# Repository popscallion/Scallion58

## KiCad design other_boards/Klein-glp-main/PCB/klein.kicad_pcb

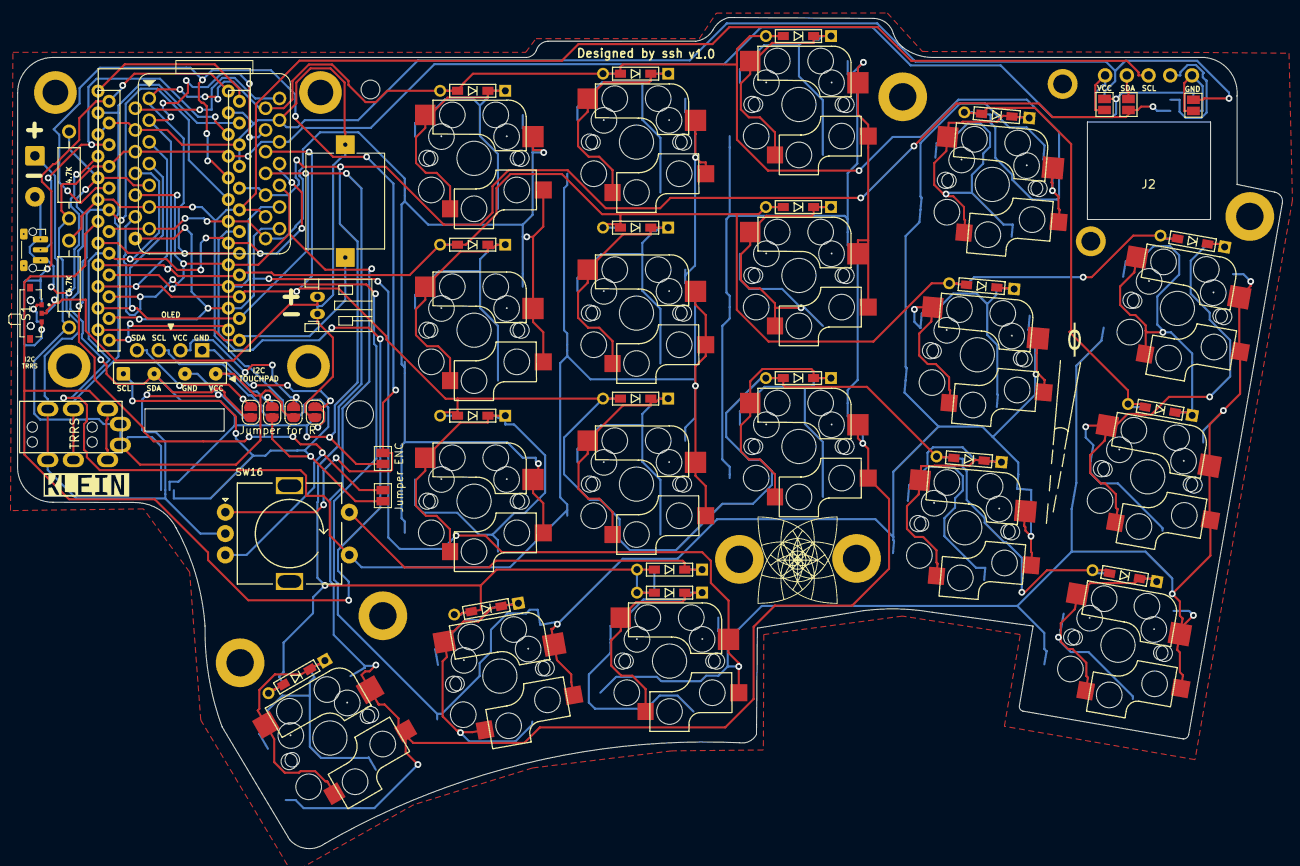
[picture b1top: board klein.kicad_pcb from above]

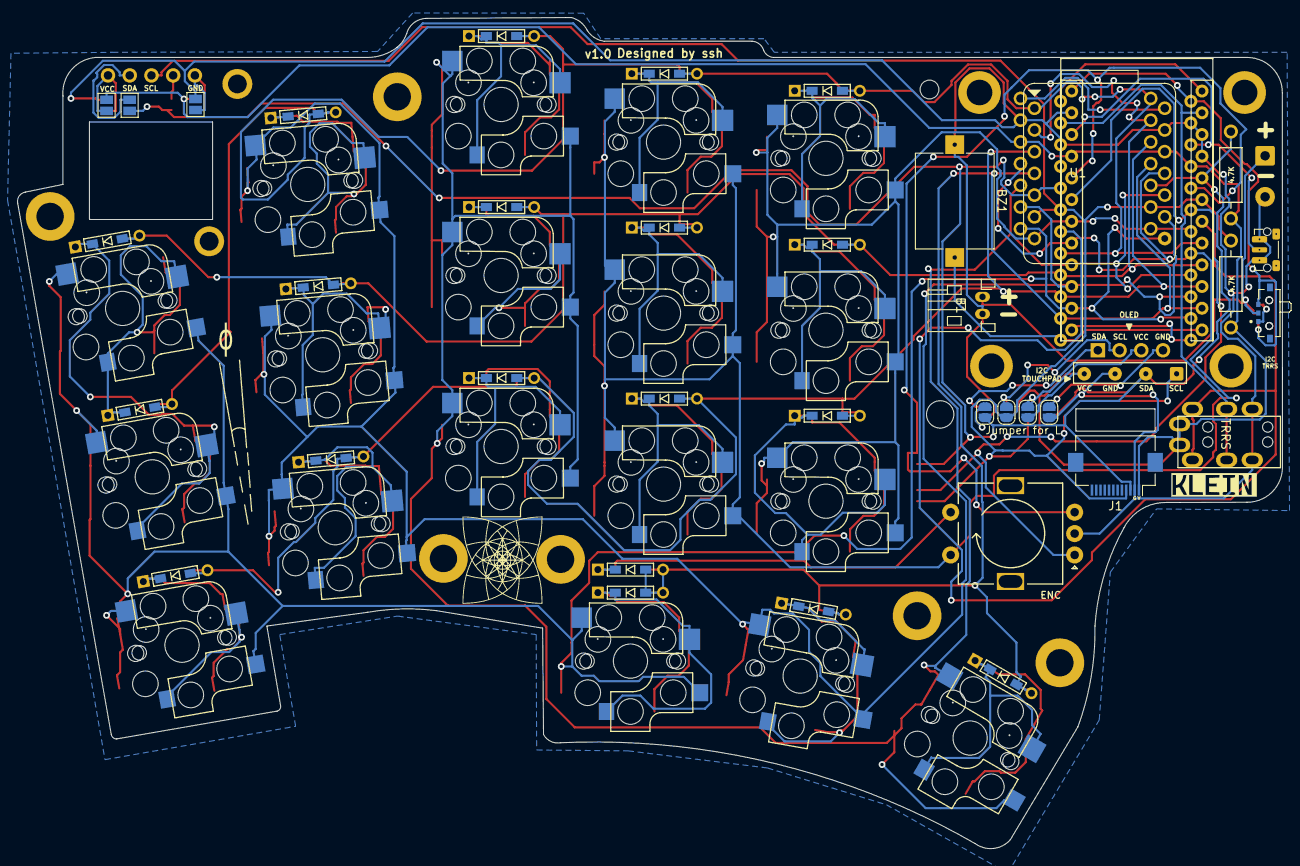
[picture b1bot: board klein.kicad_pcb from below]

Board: 2 copper layers, 147.9 x 97.2 mm, 83 parts (49 on the bottom side), 48 nets.

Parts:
B1: JST Battery; JST_PH_reversible
B2: Battery Pads; SolderWire-0.5sqmm_1x02_P4.8mm_D0.9mm_OD2.3mm
BZ1: Buzzer; Buzzer_Mallory_AST1109MLTRQ_reversible
D1, D2, D3, D4, D5, D6, D7, D8, D9, D10, D11, D12, D13, D14, D15, D16, D17, D18, D19: DIODE; D3_TH_SMD
G3, G4: LOGO; klein
G33, G34: LOGO; klein_small
H1, H2, H4, H5, H6, H8: MountingHole; MountingHole_3.2mm_M3_ISO7380_Pad
H3: MountingHole; MountingHole_3.2mm_M3
H7: MountingHole; MountingHole_2.2mm_M2
H9, H10: MountingHole; MountingHole_2.2mm_M2_ISO7380_Pad
J1: Conn_01x12; Hirose_FH12-12S-0.5SH_1x12-1MP_P0.50mm_Horizontal
J2: Haptic Buzz; Pimoroni Haptic Buzz DRV2605L Driver
J3: Conn_01x04; SolderWire-0.1sqmm_1x04_P3.6mm_D0.4mm_OD1mm
J5: OLED-128x64
JP1, JP2, JP3, JP4, JP5, JP6, JP7, JP8: Jumper_2_Open; SolderJumper-2_P1.3mm_Open_RoundedPad1.0x1.5mm
JP9, JP10: Jumper_2_Open; SolderJumper-2_P1.3mm_Open_Pad1.0x1.5mm
JP11, JP13: GND Jumper; SolderJumper-2_P1.3mm_Open_Pad1.0x1.5mm
JP12, JP14: VCC Jumper; SolderJumper-2_P1.3mm_Open_Pad1.0x1.5mm
JP16, JP17: SolderJumper_2_Open; SolderJumper-2_P1.3mm_Open_Pad1.0x1.5mm
R1, R2: 4.7K; RESISTOR
RSW1: SW_Push; SW_Push_1P1T-MP_NO_Horizontal_Alps_SKRTLAE010_both_sides
S1: EG1218; RevSlideSwitch
SW1, SW2, SW3, SW4, SW5, SW6, SW7, SW8, SW9, SW10, SW11, SW12, SW13, SW14, SW15, SW17, SW18, SW19: MX_SW_HS; MX_Choc_Hotswap_Mod
SW16: RotaryEncoder_Switch; MX-1U-EC11_Switch
T1: Trackpad_Mount; Trackpad Mount
U1: XIAO-BLE
U2: ProMicro; ProMicro_rev2
U3: TRRS; MJ-4PP-9

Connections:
AUDIO: BZ1.1 (-), U2.12 (9/B5)
BAT+: S1.3, U2.24 (RAW)
COL 0: SW1.1, SW6.1, SW11.1, U1.7 (PB08_A6_D6_TX), U2.18 (F6/A1)
COL 1: SW2.1, SW7.1, SW12.1, SW16.S1, U1.11 (PA6_A10_D10_MOSI), U2.17 (F7/A0)
COL 2: SW3.1, SW8.1, SW13.1, SW17.1, U1.10 (PA5_A9_D9_MISO), U2.16 (B1/15)
COL 3: SW4.1, SW9.1, SW14.1, SW18.1, U1.9 (PA7_A8_D8_SCK), U2.15 (B3/14)
COL 4: SW5.1, SW10.1, SW15.1, SW19.1, U1.8 (PB09_A7_D7_RX), U2.14 (B2/16)
ENC_A: JP9.2 (B), SW16.A, U2.20 (F4/A3)
ENC_B: JP10.2 (B), SW16.B, U2.19 (F5/A2)
GND: B1.2, B2.2 (-), BZ1.2 (+), J1.2, J3.3, JP1.2 (B), JP8.2 (B), JP11.1 (A), JP13.1 (A), RSW1.1, SW16.C, U1.13 (GND), U2.3 (GND), U2.4 (GND), U2.23 (GND), U3.S
unnamed: B1.1, B2.1 (+), S1.2
unnamed: D1.1 (K), SW1.2
unnamed: D2.1 (K), SW2.2
unnamed: D3.1 (K), SW3.2
unnamed: D4.1 (K), SW4.2
unnamed: D5.1 (K), SW5.2
unnamed: D6.1 (K), SW6.2
unnamed: D7.1 (K), SW7.2
unnamed: D8.1 (K), SW8.2
unnamed: D9.1 (K), SW9.2
unnamed: D10.1 (K), SW10.2
unnamed: D11.1 (K), SW11.2
unnamed: D12.1 (K), SW12.2
unnamed: D13.1 (K), SW13.2
unnamed: D14.1 (K), SW14.2
unnamed: D15.1 (K), SW15.2
unnamed: D17.1 (K), SW17.2
unnamed: D18.1 (K), SW18.2
unnamed: D19.1 (K), SW19.2
unnamed: J2.1, JP13.2 (B), JP14.2 (B)
unnamed: J2.2, JP17.1 (A)
unnamed: J2.4, JP16.1 (A)
unnamed: J2.5, JP11.2 (B), JP12.2 (B)
unnamed: J5.1 (GND), JP1.1 (A), JP5.1 (A)
unnamed: J5.2 (VCC), JP2.1 (A), JP6.1 (A)
unnamed: J5.3 (SCL), JP3.1 (A), JP7.1 (A)
unnamed: J5.4 (SDA), JP4.1 (A), JP8.1 (A)
RESET: RSW1.2, U2.22 (RST)
ROW 0: D1.2 (A), D2.2 (A), D3.2 (A), D4.2 (A), D5.2 (A), U1.1 (PA02_A0_D0), U2.8 (5/C6)
ROW 1: D6.2 (A), D7.2 (A), D8.2 (A), D9.2 (A), D10.2 (A), U1.2 (PA4_A1_D1), U2.9 (6/D7)
ROW 2: D11.2 (A), D12.2 (A), D13.2 (A), D14.2 (A), D15.2 (A), U1.3 (PA10_A2_D2), U2.10 (7/E6)
ROW 3: D16.2 (A), D17.2 (A), D18.2 (A), D19.2 (A), U1.4 (PA11_A3_D3), U2.11 (8/B4)
RX: U2.7 (4/D4), U3.R1
SCL: J1.4, J2.3, J3.1, JP3.2 (B), JP6.2 (B), JP10.1 (A), R2.2, U1.6 (PA9_A5_D5_SCL), U2.6 (3/D0/SCL)
SDA: J1.3, J3.2, JP4.2 (B), JP5.2 (B), JP9.1 (A), JP16.2 (B), JP17.2 (B), R1.2, U1.5 (PA8_A4_D4_SDA), U2.5 (2/D1/SDA)
SW16B: D16.1 (K), SW16.S2
TX: U2.2 (RX1/D2), U3.R2
VCC_3V3: J1.1, J3.4, JP2.2 (B), JP7.2 (B), JP12.1 (A), JP14.1 (A), R1.1, R2.1, U1.12 (3V3), U2.21 (VCC), U3.T

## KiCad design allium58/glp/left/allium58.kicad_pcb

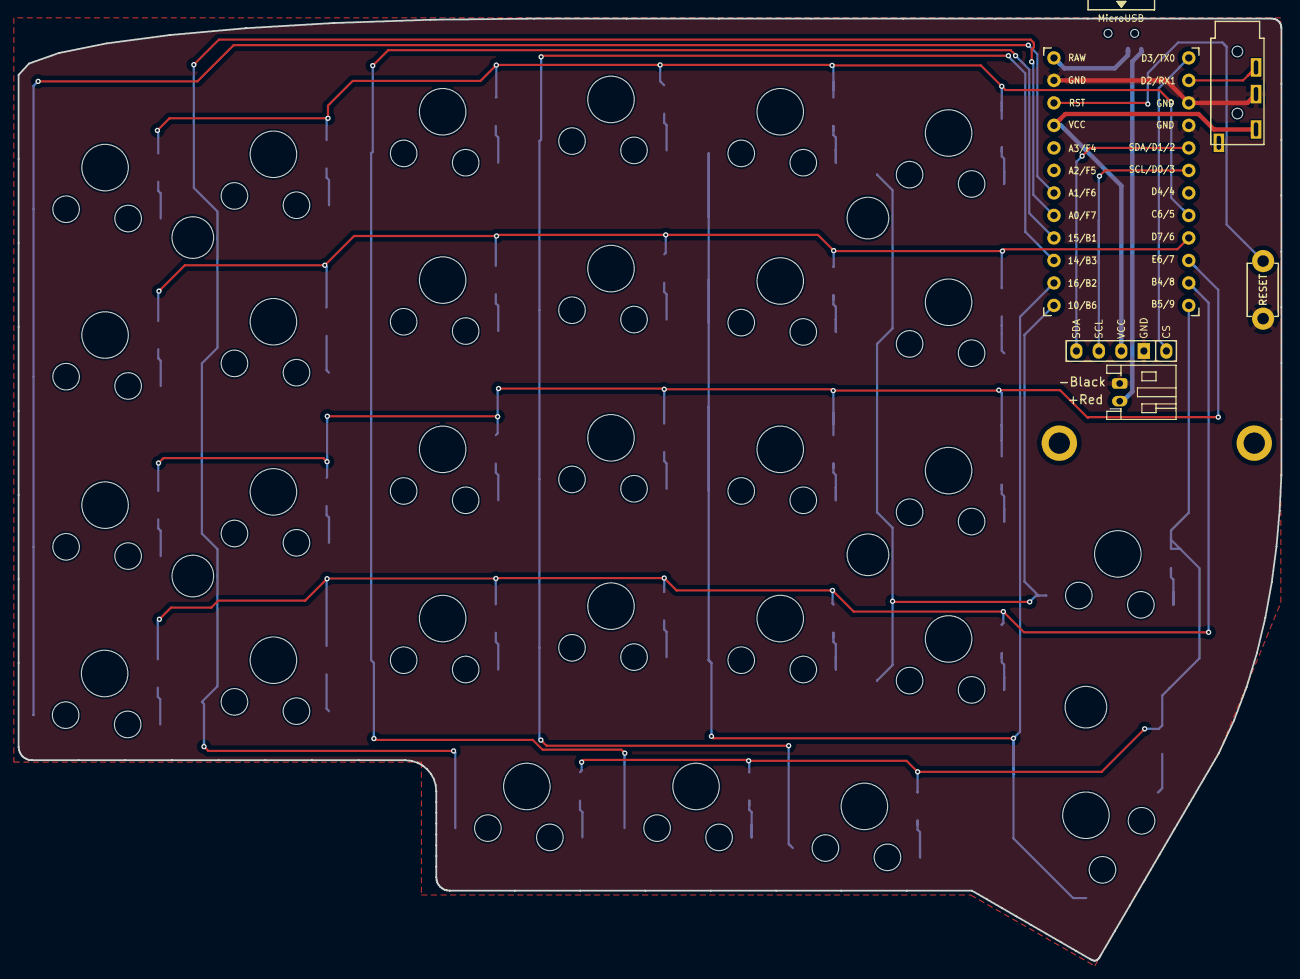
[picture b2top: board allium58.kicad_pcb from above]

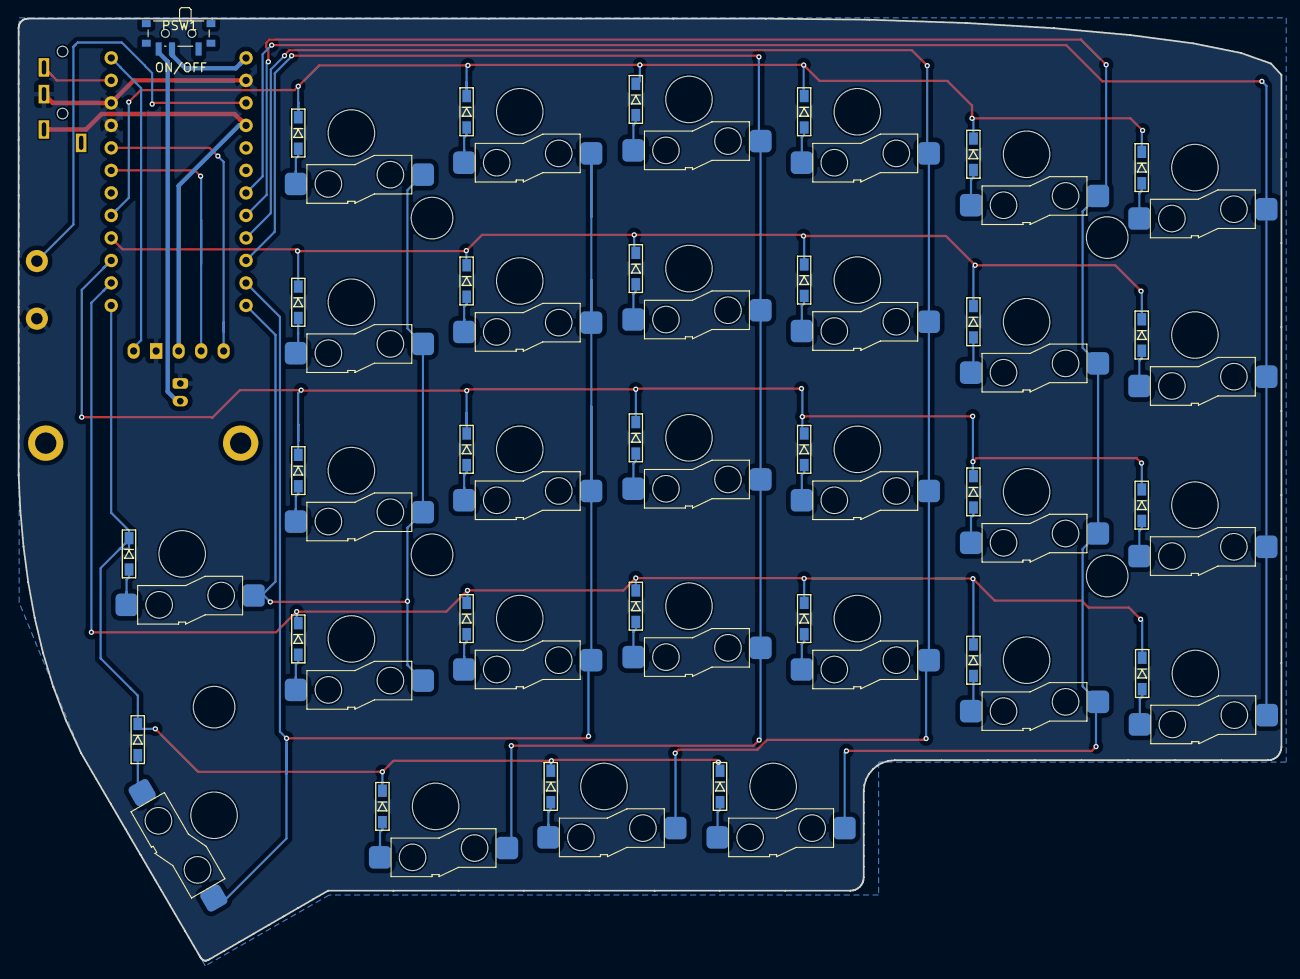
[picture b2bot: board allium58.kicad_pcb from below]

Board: 2 copper layers, 142.5 x 106.3 mm, 71 parts (37 on the bottom side), 49 nets.

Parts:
BATJ1: Conn_01x02_Female; JST_PH_S2B-PH-K_1x02_P2.00mm_Horizontal
D1, D2, D3, D4, D5, D6, D7, D8, D9, D10, D11, D12, D13, D14, D15, D16, D17, D18, D19, D20, D21, D22, D23, D24, D25, D26, D27, D28, D29: D; D3_SMD_v2
J2: 4PIN; MJ-4PP-9
J3: OLED; nice_view_1side
PSW1: SW_SPST; SW_SPDT_PCM12
RSW1: SW_RST; TACT_SWITCH_TVBP06
SW1, SW2, SW3, SW4, SW5, SW6, SW7, SW8, SW9, SW10, SW11, SW12, SW13, SW14, SW15, SW16, SW17, SW18, SW19, SW20, SW21, SW22, SW23, SW24, SW25, SW26, SW27, SW28, SW29: SW_PUSH; SW_Gateron_LowProfile_HotSwap
TH1, TH2: HOLE; M2_HOLE_PCB
TH3, TH4, TH5, TH6, TH7: HOLE; HOLE_M2_TH
U1: ProMicro; ProMicro_v3

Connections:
+BATT: BATJ1.1, PSW1.3 (C)
CS: J3.5, U1.1 (TX(PD3))
DATA: J2.3, U1.2 (RX(PD2))
GND: BATJ1.2, J2.2, J3.4, RSW1.1, U1.3 (GND), U1.4 (GND), U1.23 (GND)
unnamed: D1.2 (A), SW1.2
unnamed: D2.2 (A), SW2.2
unnamed: D3.2 (A), SW3.2
unnamed: D4.2 (A), SW4.2
unnamed: D5.2 (A), SW5.2
unnamed: D6.2 (A), SW6.2
unnamed: D7.2 (A), SW7.2
unnamed: D8.2 (A), SW8.2
unnamed: D9.2 (A), SW9.2
unnamed: D10.2 (A), SW10.2
unnamed: D11.2 (A), SW11.2
unnamed: D12.2 (A), SW12.2
unnamed: D13.2 (A), SW13.2
unnamed: D14.2 (A), SW14.2
unnamed: D15.2 (A), SW15.2
unnamed: D16.2 (A), SW16.2
unnamed: D17.2 (A), SW17.2
unnamed: D18.2 (A), SW18.2
unnamed: D19.2 (A), SW19.2
unnamed: D20.2 (A), SW20.2
unnamed: D21.2 (A), SW21.2
unnamed: D22.2 (A), SW22.2
unnamed: D23.2 (A), SW23.2
unnamed: D24.2 (A), SW24.2
unnamed: D25.2 (A), SW25.2
unnamed: D26.2 (A), SW26.2
unnamed: D27.2 (A), SW27.2
unnamed: D28.2 (A), SW28.2
unnamed: D29.2 (A), SW29.2
RESET: RSW1.2, U1.22 (RST)
SCL: J3.2, U1.6 (SCL(PD0))
SDA: J3.1, U1.5 (SDA(PD1))
VCC: J2.1, J3.3, U1.21 (VCC)
col0: SW6.1, SW12.1, SW18.1, SW24.1, U1.18 (A1(PF6))
col1: SW5.1, SW11.1, SW17.1, SW23.1, SW29.1, U1.17 (A0(PF7))
col2: SW4.1, SW10.1, SW16.1, SW22.1, SW28.1, U1.16 (D15(PB1))
col3: SW3.1, SW9.1, SW15.1, SW21.1, SW27.1, U1.15 (D14(PB3))
col4: SW2.1, SW8.1, SW14.1, SW20.1, SW26.1, U1.14 (D16(PB2))
col5: SW1.1, SW7.1, SW13.1, SW19.1, SW25.1, U1.13 (D10(PB6))
raw: PSW1.2 (B), U1.24 (RAW)
row0: D1.1 (K), D2.1 (K), D3.1 (K), D4.1 (K), D5.1 (K), D6.1 (K), U1.8 (D5(PC6))
row1: D7.1 (K), D8.1 (K), D9.1 (K), D10.1 (K), D11.1 (K), D12.1 (K), U1.9 (D6(PD7))
row2: D13.1 (K), D14.1 (K), D15.1 (K), D16.1 (K), D17.1 (K), D18.1 (K), U1.10 (D7(PE6))
row3: D19.1 (K), D20.1 (K), D21.1 (K), D22.1 (K), D23.1 (K), D24.1 (K), U1.11 (D8(PB4))
row4: D25.1 (K), D26.1 (K), D27.1 (K), D28.1 (K), D29.1 (K), U1.12 (D9(PB5))

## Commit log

2025-06-14 add unicorne keymap
2025-06-14 update combo term to 25
2025-06-14 fix rbrc combo
2025-06-14 fix rbrc
2025-06-14 add globe arrow for home end etc
2025-06-14 working home, end, pgup pgdown—intercepting events
2025-06-14 fix f11 and f12
2025-06-14 actually fix f11 f12
